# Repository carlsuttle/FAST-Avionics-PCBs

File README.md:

# FAST Avionics PCBs

KiCad 10 hardware designs for FAST avionics.

## Projects

- `FLIGHT CONTROLLER/` — FAST flight-controller schematic, PCB, fabrication outputs, component libraries, and design notes.
- `AS_GPS_XIAO_OUTBOARD/` — GPS/XIAO outboard schematic, PCB, fabrication outputs, and supporting libraries.

Open each `.kicad_pro` file with KiCad 10 or newer.

Local KiCad preferences, lock files, autosaves, backups, and history snapshots are intentionally excluded from version control.

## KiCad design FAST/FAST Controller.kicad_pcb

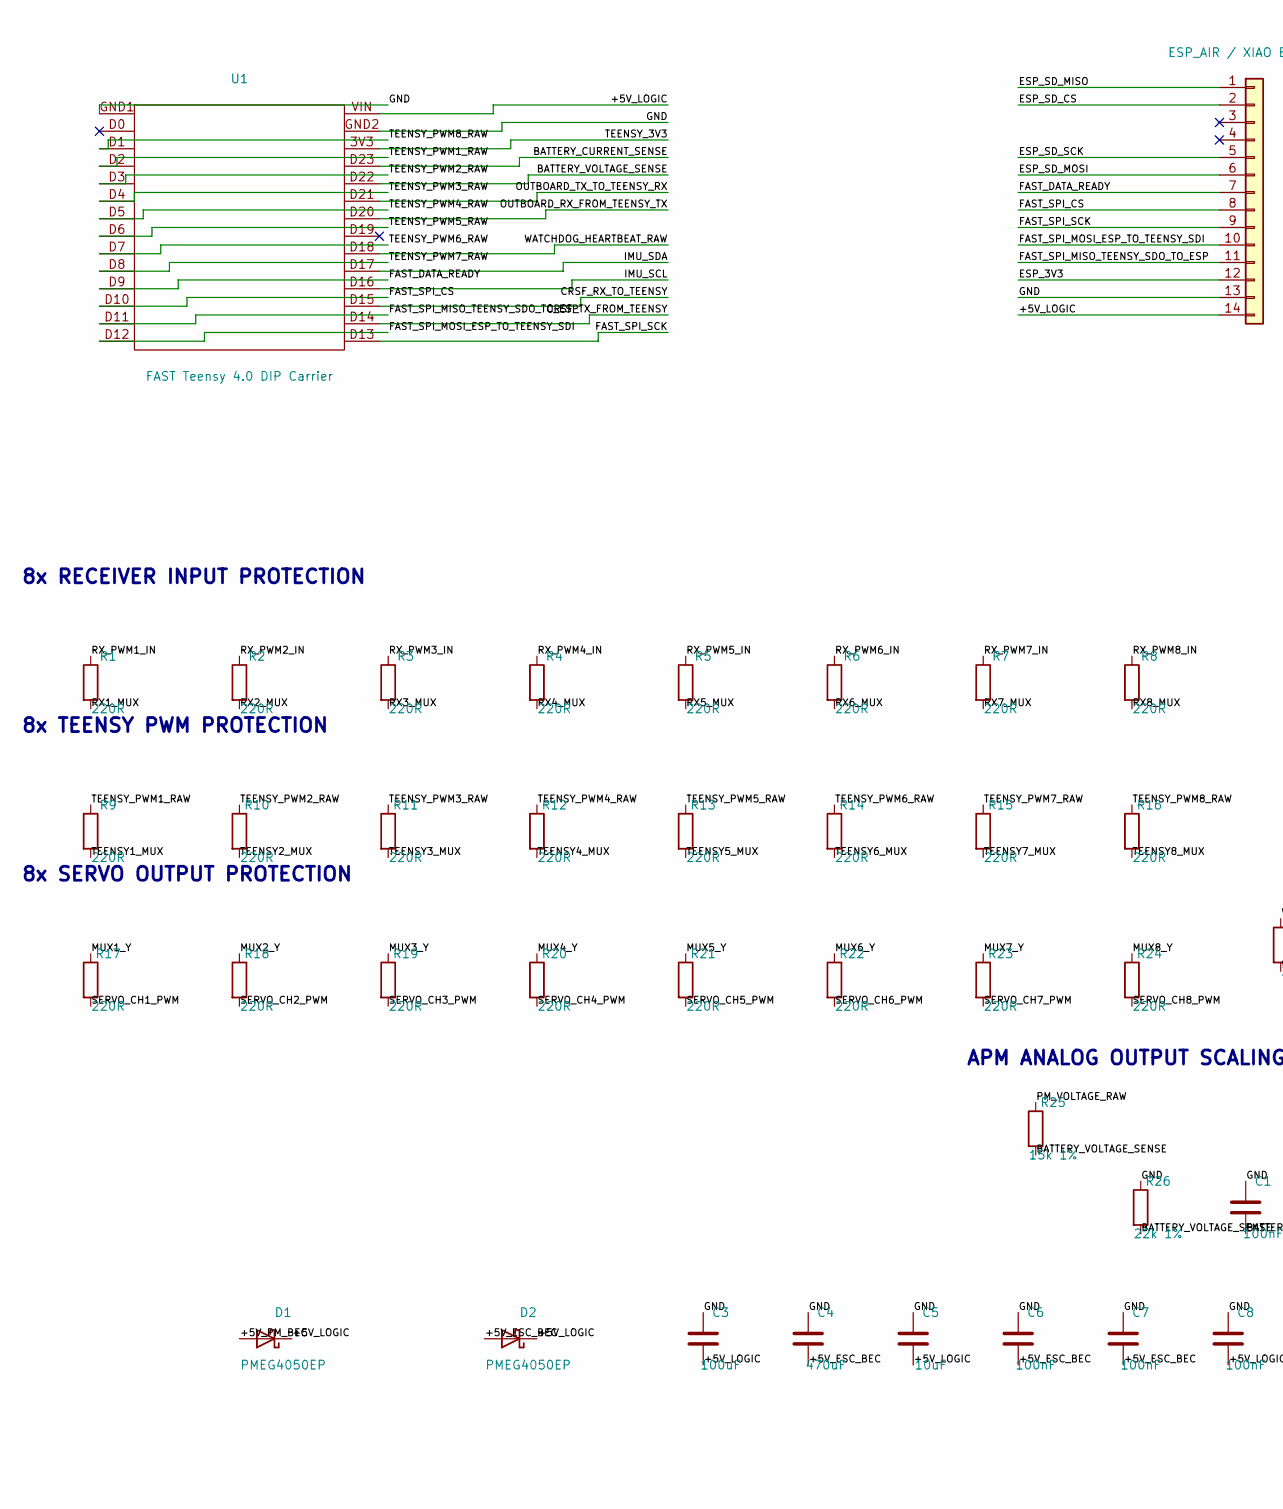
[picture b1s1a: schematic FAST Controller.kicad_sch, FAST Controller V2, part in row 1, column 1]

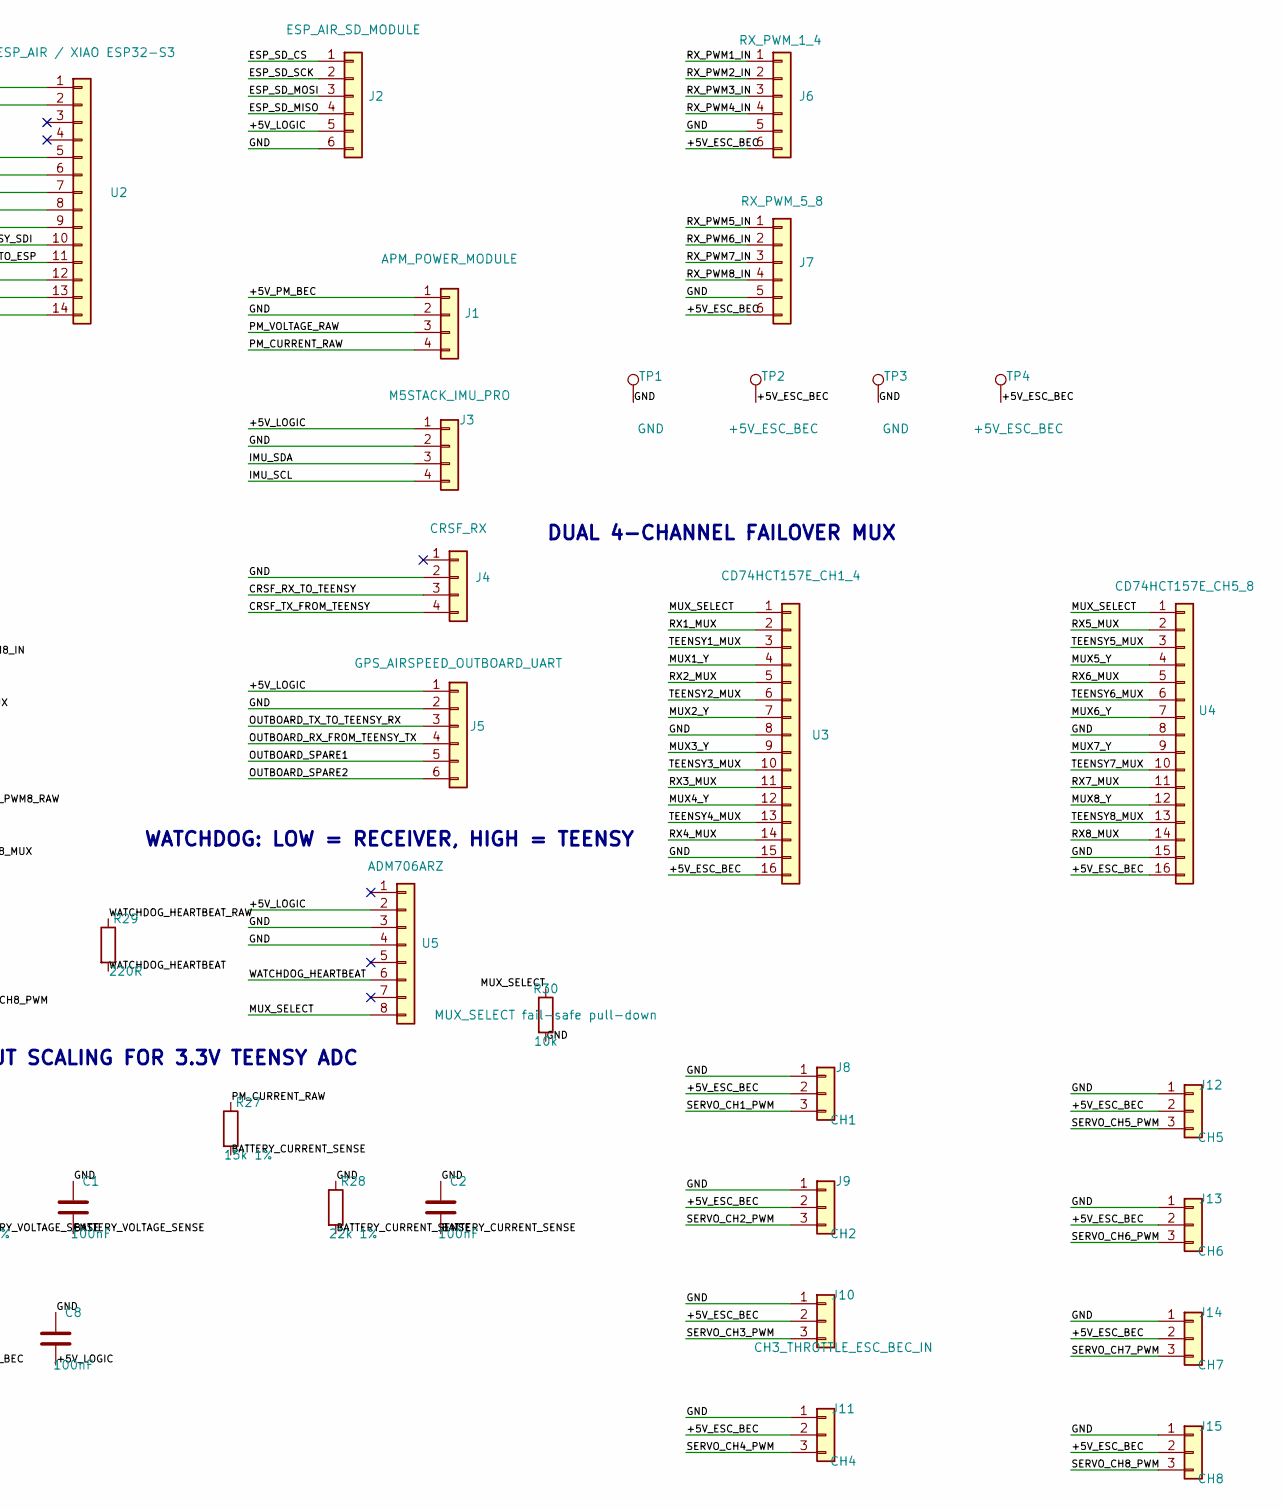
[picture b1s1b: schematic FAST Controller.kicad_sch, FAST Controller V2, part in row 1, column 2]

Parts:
C1, C2, C6, C7, C8: 100nF; C_0805_2012Metric_Pad1.18x1.45mm_HandSolder
C3: 100uF; CP_Radial_D5.0mm_P2.00mm
C4: 470uF; CP_Radial_D8.0mm_P3.50mm
C5: 10uF; C_0805_2012Metric_Pad1.18x1.45mm_HandSolder
D1, D2: PMEG4050EP; D_SOD-128
J1: APM_POWER_MODULE; JST_XH_B4B-XH-A_1x04_P2.50mm_Vertical
J2: ESP_AIR_SD_MODULE; JST_XH_B6B-XH-A_1x06_P2.50mm_Vertical
J3: M5STACK_IMU_PRO; JST_XH_B4B-XH-A_1x04_P2.50mm_Vertical
J4: CRSF_RX; JST_XH_B4B-XH-A_1x04_P2.50mm_Vertical
J5: GPS_AIRSPEED_OUTBOARD_UART; JST_XH_B6B-XH-A_1x06_P2.50mm_Vertical
J6: RX_PWM_1_4; JST_XH_B6B-XH-A_1x06_P2.50mm_Vertical
J7: RX_PWM_5_8; JST_XH_B6B-XH-A_1x06_P2.50mm_Vertical
J8: CH1; PinHeader_1x03_P2.54mm_Vertical
J9: CH2; PinHeader_1x03_P2.54mm_Vertical
J10: CH3_THROTTLE_ESC_BEC_IN; PinHeader_1x03_P2.54mm_Vertical
J11: CH4; PinHeader_1x03_P2.54mm_Vertical
J12: CH5; PinHeader_1x03_P2.54mm_Vertical
J13: CH6; PinHeader_1x03_P2.54mm_Vertical
J14: CH7; PinHeader_1x03_P2.54mm_Vertical
J15: CH8; PinHeader_1x03_P2.54mm_Vertical
R1, R2, R3, R4, R5, R6, R7, R8, R9, R10, R11, R12, R13, R14, R15, R16, R17, R18, R19, R20, R21, R22, R23, R24, R29: 220R; R_0805_2012Metric_Pad1.20x1.40mm_HandSolder
R25, R27: 15k 1%; R_0805_2012Metric_Pad1.20x1.40mm_HandSolder
R26, R28: 22k 1%; R_0805_2012Metric_Pad1.20x1.40mm_HandSolder
R30: 10k; R_0805_2012Metric_Pad1.20x1.40mm_HandSolder
TP1, TP3: GND; TestPoint_THTPad_D1.5mm_Drill0.7mm
TP2, TP4: +5V_ESC_BEC; TestPoint_THTPad_D1.5mm_Drill0.7mm
U1: FAST Teensy 4.0 DIP Carrier; FAST_Teensy40_DIP_Carrier
U2: ESP_AIR / XIAO ESP32-S3; XIAO-ESP32-S3-DIP
U3: CD74HCT157E_CH1_4; DIP-16_W7.62mm_LongPads
U4: CD74HCT157E_CH5_8; DIP-16_W7.62mm_LongPads
U5: ADM706ARZ; SOIC-8_3.9x4.9mm_P1.27mm

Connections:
/+5V_ESC_BEC: C4.1, C6.2, C7.2, D2.2 (A), J6.6, J7.6, J8.2, J9.2, J10.2, J11.2, J12.2, J13.2, J14.2, J15.2, TP2.1, TP4.1, U3.16, U4.16
/+5V_LOGIC: C3.1, C5.2, C8.2, D1.1 (K), D2.1 (K), J2.5, J3.1, J5.1, U1.VIN (VIN_/_5V), U2.14, U5.2
/+5V_PM_BEC: D1.2 (A), J1.1
/BATTERY_CURRENT_SENSE: C2.2, R27.2, R28.2, U1.D23 (D23_/_A9)
/BATTERY_VOLTAGE_SENSE: C1.2, R25.2, R26.2, U1.D22 (D22_/_A8)
/CRSF_RX_TO_TEENSY: J4.3, U1.D15 (D15_/_A1)
/CRSF_TX_FROM_TEENSY: J4.4, U1.D14 (D14_/_A0)
/ESP_3V3: U2.12
/ESP_SD_CS: J2.1, U2.2
/ESP_SD_MISO: J2.4, U2.1
/ESP_SD_MOSI: J2.3, U2.6
/ESP_SD_SCK: J2.2, U2.5
/FAST_DATA_READY: U1.D9 (D9_/_DATA_READY), U2.7
/FAST_SPI_CS: U1.D10 (D10_/_CS), U2.8
/FAST_SPI_MISO_TEENSY_SDO_TO_ESP: U1.D11 (D11_/_SPI_SDO), U2.11
/FAST_SPI_MOSI_ESP_TO_TEENSY_SDI: U1.D12 (D12_/_SPI_SDI), U2.10
/FAST_SPI_SCK: U1.D13 (D13_/_SCK_/_LED), U2.9
/GND: C1.1, C2.1, C3.2, C4.2, C5.1, C6.1, C7.1, C8.1, J1.2, J2.6, J3.2, J4.2, J5.2, J6.5, J7.5, J8.1, J9.1, J10.1, J11.1, J12.1, J13.1, J14.1, J15.1, R26.1, R28.1, R30.2, TP1.1, TP3.1, U1.GND1 (GND), U1.GND2 (GND), U2.13, U3.8, U3.15, U4.8, U4.15, U5.3, U5.4
/IMU_SCL: J3.4, U1.D16 (D16_/_A2)
/IMU_SDA: J3.3, U1.D17 (D17_/_A3)
/MUX1_Y: R17.1, U3.4
/MUX2_Y: R18.1, U3.7
/MUX3_Y: R19.1, U3.9
/MUX4_Y: R20.1, U3.12
/MUX5_Y: R21.1, U4.4
/MUX6_Y: R22.1, U4.7
/MUX7_Y: R23.1, U4.9
/MUX8_Y: R24.1, U4.12
/MUX_SELECT: R30.1, U3.1, U4.1, U5.8
/OUTBOARD_RX_FROM_TEENSY_TX: J5.4, U1.D20 (D20_/_A6)
/OUTBOARD_SPARE1: J5.5
/OUTBOARD_SPARE2: J5.6
/OUTBOARD_TX_TO_TEENSY_RX: J5.3, U1.D21 (D21_/_A7)
/PM_CURRENT_RAW: J1.4, R27.1
/PM_VOLTAGE_RAW: J1.3, R25.1
/RX1_MUX: R1.2, U3.2
/RX2_MUX: R2.2, U3.5
/RX3_MUX: R3.2, U3.11
/RX4_MUX: R4.2, U3.14
/RX5_MUX: R5.2, U4.2
/RX6_MUX: R6.2, U4.5
/RX7_MUX: R7.2, U4.11
/RX8_MUX: R8.2, U4.14
/RX_PWM1_IN: J6.1, R1.1
/RX_PWM2_IN: J6.2, R2.1
/RX_PWM3_IN: J6.3, R3.1
/RX_PWM4_IN: J6.4, R4.1
/RX_PWM5_IN: J7.1, R5.1
/RX_PWM6_IN: J7.2, R6.1
/RX_PWM7_IN: J7.3, R7.1
/RX_PWM8_IN: J7.4, R8.1
/SERVO_CH1_PWM: J8.3, R17.2
/SERVO_CH2_PWM: J9.3, R18.2
/SERVO_CH3_PWM: J10.3, R19.2
/SERVO_CH4_PWM: J11.3, R20.2
/SERVO_CH5_PWM: J12.3, R21.2
/SERVO_CH6_PWM: J13.3, R22.2
/SERVO_CH7_PWM: J14.3, R23.2
/SERVO_CH8_PWM: J15.3, R24.2
/TEENSY1_MUX: R9.2, U3.3
/TEENSY2_MUX: R10.2, U3.6
/TEENSY3_MUX: R11.2, U3.10
/TEENSY4_MUX: R12.2, U3.13
/TEENSY5_MUX: R13.2, U4.3
/TEENSY6_MUX: R14.2, U4.6
/TEENSY7_MUX: R15.2, U4.10
/TEENSY8_MUX: R16.2, U4.13
/TEENSY_3V3: U1.3V3
/TEENSY_PWM1_RAW: R9.1, U1.D2
/TEENSY_PWM2_RAW: R10.1, U1.D3
/TEENSY_PWM3_RAW: R11.1, U1.D4
/TEENSY_PWM4_RAW: R12.1, U1.D5
/TEENSY_PWM5_RAW: R13.1, U1.D6
/TEENSY_PWM6_RAW: R14.1, U1.D7
/TEENSY_PWM7_RAW: R15.1, U1.D8
/TEENSY_PWM8_RAW: R16.1, U1.D1 (D1_/_TX1)
/WATCHDOG_HEARTBEAT: R29.2, U5.6
/WATCHDOG_HEARTBEAT_RAW: R29.1, U1.D18 (D18_/_A4_/_SDA)

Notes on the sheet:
8x RECEIVER INPUT PROTECTION
APM ANALOG OUTPUT SCALING FOR 3.3V TEENSY ADC
8x TEENSY PWM PROTECTION
WATCHDOG: LOW = RECEIVER, HIGH = TEENSY
8x SERVO OUTPUT PROTECTION
DUAL 4-CHANNEL FAILOVER MUX

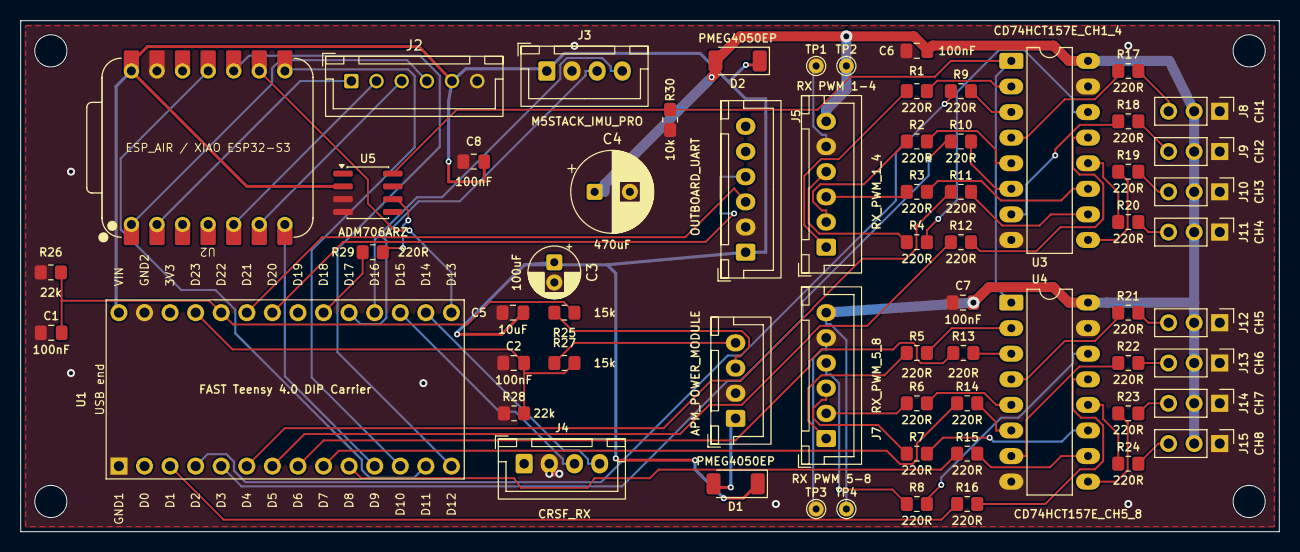
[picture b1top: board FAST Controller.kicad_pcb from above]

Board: 2 copper layers, 125.0 x 50.8 mm, 68 parts (0 on the bottom side), 74 nets.

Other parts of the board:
H1, H2, H3, H4: MountingHole_3.2mm_M3

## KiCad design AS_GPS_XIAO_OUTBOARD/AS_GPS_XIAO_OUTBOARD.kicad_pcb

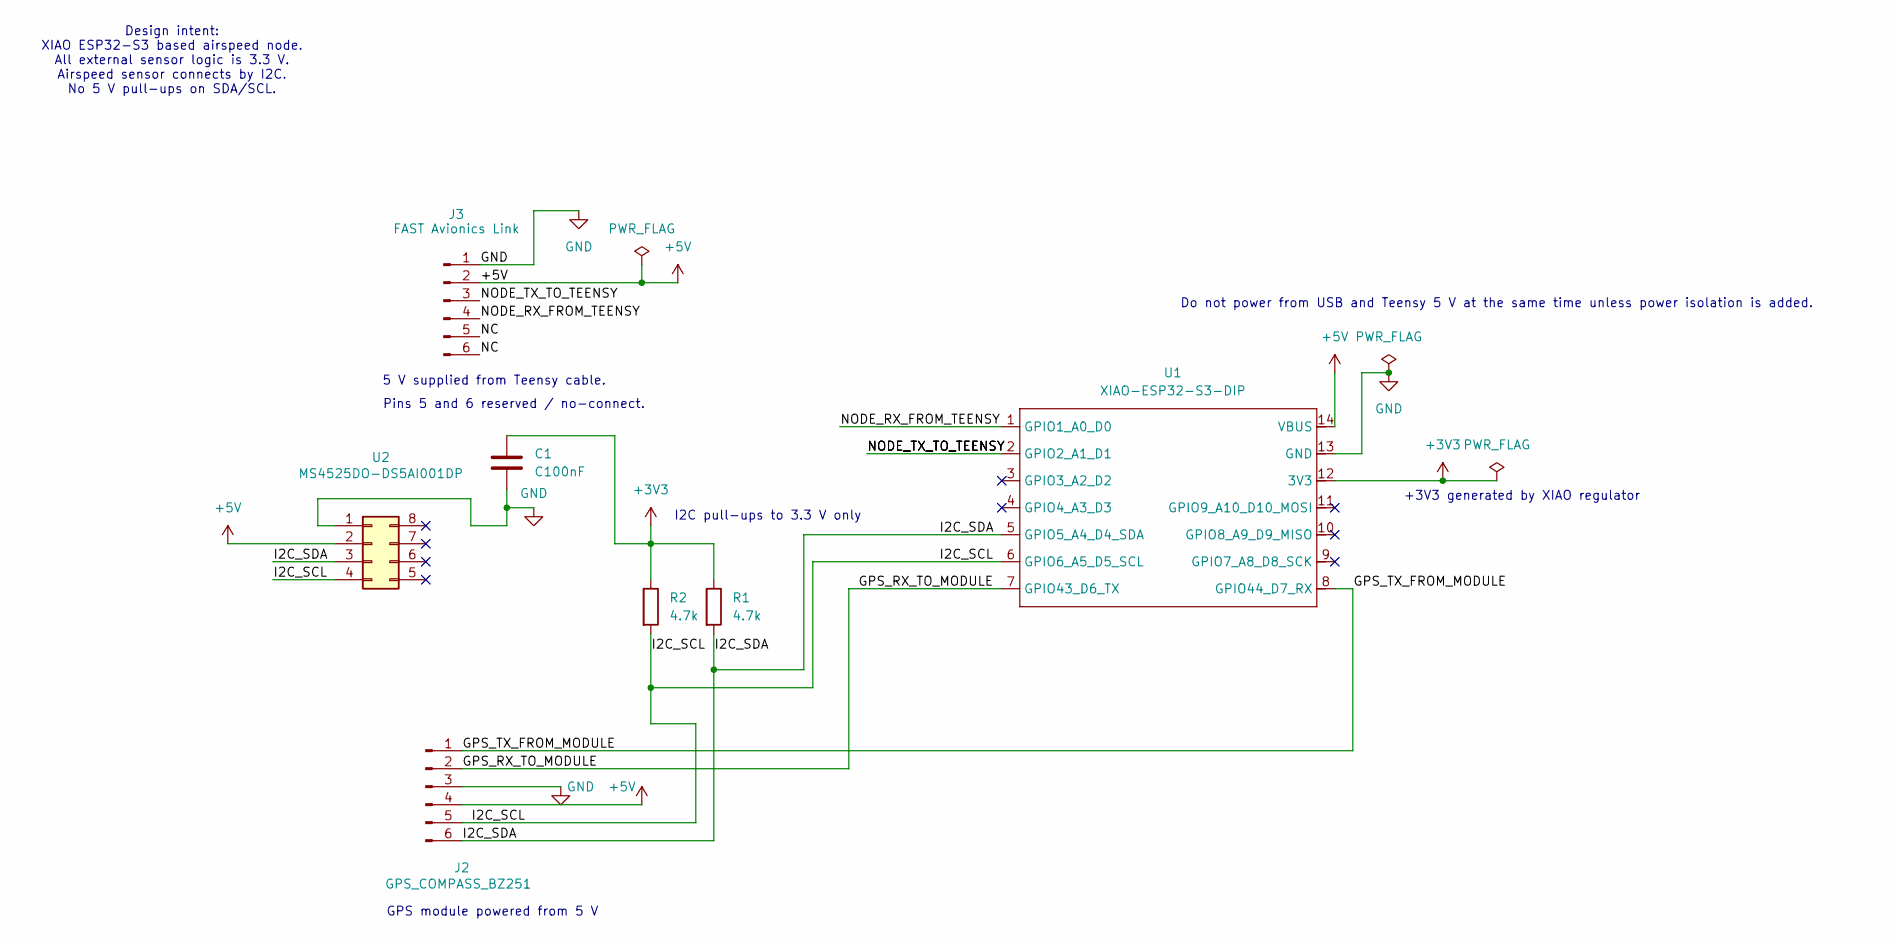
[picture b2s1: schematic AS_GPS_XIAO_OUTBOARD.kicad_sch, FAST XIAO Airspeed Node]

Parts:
C1: C100nF; C_0805_2012Metric
J2: GPS_COMPASS_BZ251; JST_XH_B6B-XH-A_1x06_P2.50mm_Vertical
J3: FAST Avionics Link; JST_XH_B6B-XH-A_1x06_P2.50mm_Vertical
R1, R2: 4.7k; R_0805_2012Metric
U1: XIAO-ESP32-S3-DIP
U2: MS4525DO-DS5AI001DP; DIP-8_W7.62mm

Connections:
+3V3: C1.1, R1.1, R2.1, U1.12 (3V3)
+5V: J2.4, J3.2, U1.14 (VBUS), U2.2
/GPS_RX_TO_MODULE: J2.2, U1.7 (GPIO43_D6_TX)
/GPS_TX_FROM_MODULE: J2.1, U1.8 (GPIO44_D7_RX)
/I2C_SCL: J2.5, R2.2, U1.6 (GPIO6_A5_D5_SCL), U2.4
/I2C_SDA: J2.6, R1.2, U1.5 (GPIO5_A4_D4_SDA), U2.3
/NC: J3.5, J3.6
/NODE_RX_FROM_TEENSY: J3.4, U1.1 (GPIO1_A0_D0)
/NODE_TX_TO_TEENSY: J3.3, U1.2 (GPIO2_A1_D1)
GND: C1.2, J2.3, J3.1, U1.13 (GND), U2.1

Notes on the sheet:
I2C pull-ups to 3.3 V only
GPS module powered from 5 V
+3V3 generated by XIAO regulator
Pins 5 and 6 reserved / no-connect.
Do not power from USB and Teensy 5 V at the same time unless power isolation is added.
5 V supplied from Teensy cable.
Design intent: XIAO ESP32-S3 based airspeed node. All external sensor logic is 3.3 V. Airspeed sensor connects by I2C. No 5 V pull-ups on SDA/SCL.

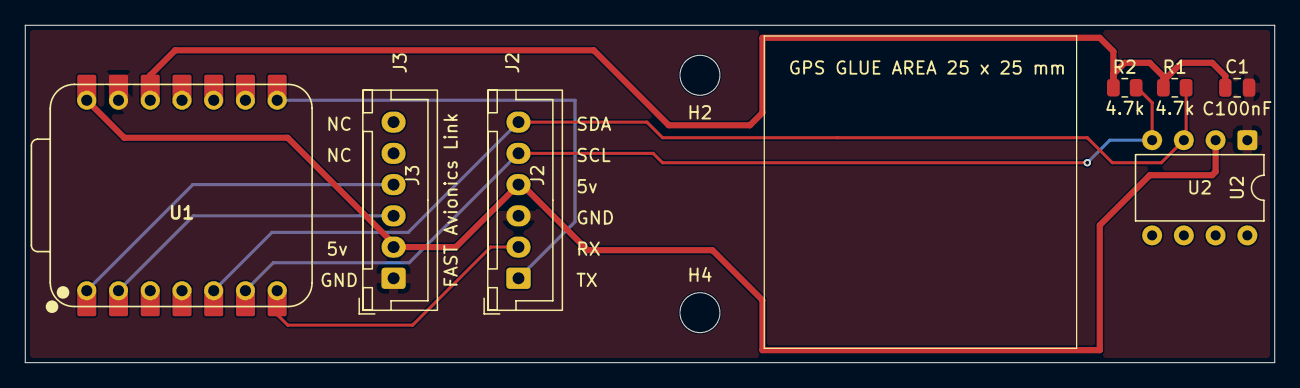
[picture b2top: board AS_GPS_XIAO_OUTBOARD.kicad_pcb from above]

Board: 2 copper layers, 100.0 x 27.0 mm, 9 parts (0 on the bottom side), 10 nets.

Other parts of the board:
H2, H4: 3.2mm_M3; MountingHole_3.2mm_M3
